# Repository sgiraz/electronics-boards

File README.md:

Electronics Boards
==================

This is the `electronics-boards` repository, containing all the electronic boards developed for study and DIY purposes.

Each board has an own folder where there are schematic, layout, firmware, simulations, documents, photos, configuration files, etc.

The board folders follow these rules:
- foldername **name of the board** 
- admitted subfolders:
   - **docs** folder contains documents
      - **datasheet** folder contains useful datasheet
      - **manuals** folder contains reference manual
   - **output** folder contains files for the production of the PCB and board (Gerber files, BOM, PCB Notes, etc.)
   - **kicad** folder contains the KiCad project
   - **pics** folder contains useful photos and videos of pcb, board, setup
   - **sw** folder contains the firmware useful for the board (test, normal operation, etc)
   
Note: folders and files must be named in lowercase

## Git LFS remark
This repository exploits the Git Large File Support ([LFS][1]) to handle the binary files.
To download the binary files, follow the GitHub [instructions][2]. To configure Git LFS, follow these [instructions][3].

[1]: https://git-lfs.github.com/
[2]: https://help.github.com/articles/installing-git-large-file-storage/
[3]: https://help.github.com/en/github/managing-large-files/configuring-git-large-file-storage

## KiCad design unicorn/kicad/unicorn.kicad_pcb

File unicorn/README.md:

# The Unicorn Board

## Overview

The Unicorn Board, designed by Simone Girardi in 2022, is a compact, Arduino-like programmable board. It's equipped with service LEDs for TX and RX, making it a versatile tool for various microcontroller projects.

## Features

- **ATmega328P Microcontroller**: Powers your projects.
- **16MHz Crystal Oscillator**: Provides a stable clock signal.
- **Input Voltage**: Accepts an external power supply ranging from 7V to 12V.
- **7805 Voltage Regulator**: Ensures a steady 5V supply to the microcontroller and other components.
- **TX and RX LEDs**: Offer visual feedback for data transmission and reception.
- **ISP Header**: Facilitates easy programming.
- **Reset Button**: Allows for easy resetting.

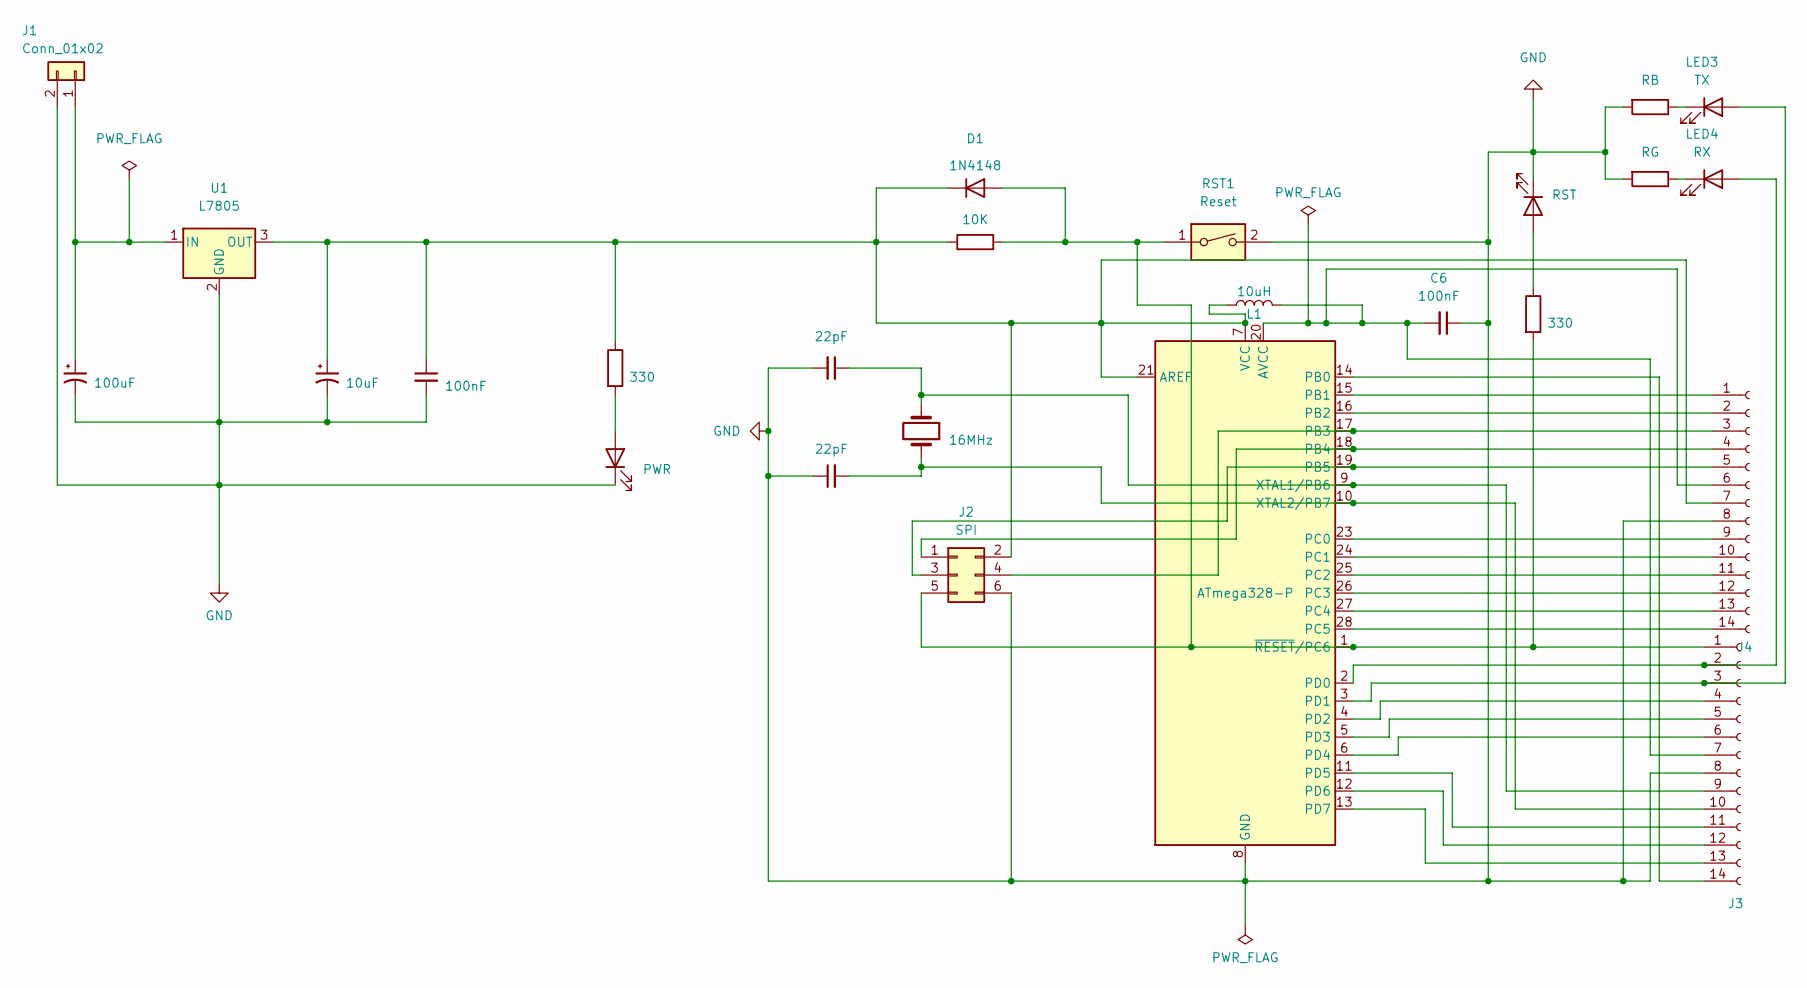
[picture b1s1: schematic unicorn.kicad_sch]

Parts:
C1: 100uF; CP_Radial_D5.0mm_P2.00mm
C2: 10uF; CP_Radial_D5.0mm_P2.00mm
C3, C6: 100nF; C_Disc_D3.8mm_W2.6mm_P2.50mm
C4, C5: 22pF; C_Disc_D3.8mm_W2.6mm_P2.50mm
Crystal1: 16MHz; Crystal_HC49-4H_Vertical
D1: 1N4148; D_DO-35_SOD27_P7.62mm_Horizontal
J1: Conn_01x02; JST_S2B-PH-SM4-TB
J2: SPI; PinHeader_2x03_P2.54mm_Vertical
J3, J4: Conn_01x14_Female; PinSocket_1x14_P2.54mm_Vertical
L1: 10uH; L_0805_2012Metric_Pad1.05x1.20mm_HandSolder
LED1: PWR; LED_D3.0mm
LED2: RST; LED_D3.0mm
LED3: TX; LED_0402_1005Metric
LED4: RX; LED_0402_1005Metric
R1, R3: 330; R_Axial_DIN0204_L3.6mm_D1.6mm_P5.08mm_Horizontal
R2: 10K; R_Axial_DIN0207_L6.3mm_D2.5mm_P10.16mm_Horizontal
R4: RB; R_0402_1005Metric
R5: RG; R_0402_1005Metric
RST1: Reset; SW_PUSH_6mm
U1: L7805; TO255P1020X450X2000-3
U2: ATmega328-P; DIP-28_W7.62mm

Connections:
GND: C1.2, C2.2, C3.2, C4.2, C5.1, C6.1, J1.2, J2.6, J3.8, J4.8, LED1.1 (K), LED2.1 (K), R4.2, R5.2, RST1.2, U1.2 (GND), U2.8 (GND), U2.22 (GND)
unnamed: D1.2 (A), J2.5, J3.1, R2.2, R3.2, RST1.1, U2.1 (~RESET/PC6)
unnamed: C2.1, C3.1, D1.1 (K), J2.2, J4.7, L1.1, R1.1, R2.1, U1.3 (OUT), U2.7 (VCC), U2.21 (AREF)
unnamed: C1.1, J1.1, U1.1 (IN)
unnamed: J2.1, J4.4, U2.18 (PB4)
unnamed: J2.3, J4.5, U2.19 (PB5)
unnamed: J2.4, J4.3, U2.17 (PB3)
unnamed: J3.2, LED4.2 (A), U2.2 (PD0)
unnamed: J3.3, LED3.2 (A), U2.3 (PD1)
unnamed: J3.4, U2.4 (PD2)
unnamed: J3.5, U2.5 (PD3)
unnamed: J3.6, U2.6 (PD4)
unnamed: C6.2, J3.7, J4.6, L1.2, U2.20 (AVCC)
unnamed: C4.1, Crystal1.1, J3.9, U2.9 (XTAL1/PB6)
unnamed: C5.2, Crystal1.2, J3.10, U2.10 (XTAL2/PB7)
unnamed: J3.11, U2.11 (PD5)
unnamed: J3.12, U2.12 (PD6)
unnamed: J3.13, U2.13 (PD7)
unnamed: J3.14, U2.14 (PB0)
unnamed: J4.1, U2.15 (PB1)
unnamed: J4.2, U2.16 (PB2)
unnamed: J4.9, U2.23 (PC0)
unnamed: J4.10, U2.24 (PC1)
unnamed: J4.11, U2.25 (PC2)
unnamed: J4.12, U2.26 (PC3)
unnamed: J4.13, U2.27 (PC4)
unnamed: J4.14, U2.28 (PC5)
unnamed: LED1.2 (A), R1.2
unnamed: LED2.2 (A), R3.1
unnamed: LED3.1 (K), R4.1
unnamed: LED4.1 (K), R5.1

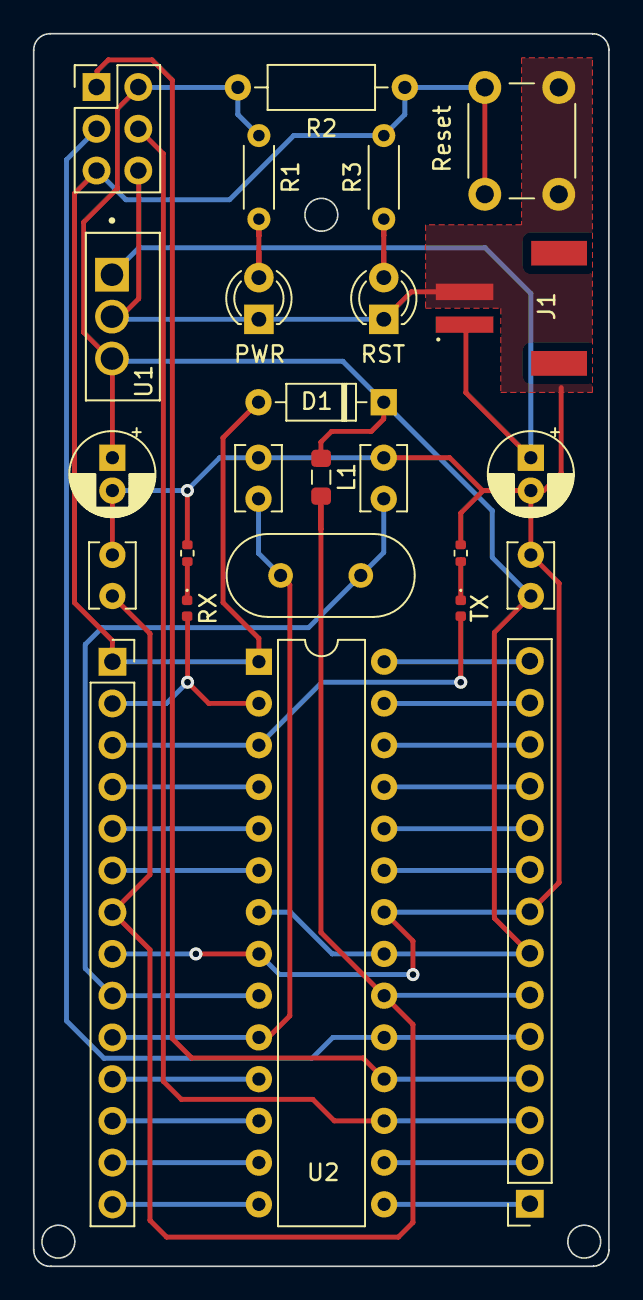
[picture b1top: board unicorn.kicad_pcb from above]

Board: 2 copper layers, 35.0 x 75.0 mm, 25 parts (0 on the bottom side), 31 nets.

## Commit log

2023-08-03 First commit: - add unicorn board - add gitignore - add datasheets
2023-08-04 update pcb: - add relative path to step file for L7805 component
2023-08-04 add fp anch sym table settings and fix the projects
2023-08-08 add step file of the unicorn board
2023-08-08 unicorn: update project file
2023-08-08 unicorn: remove step and add stl
2023-10-06 add issue template
2023-10-10 replace power connector - still need to redo routing
2024-01-04 fix routing + replace power connector with the right one
2024-01-05 add jst connector + update step file
2024-01-05 Unicorn - Feat/fix components (#2)
    * replace power connector
    - still need to redo routing
    * fix routing + replace power connector with the right one
    * add jst connector + update step file
2024-02-04 add .gitattributes for git LFS
2024-02-05 update unicorn board layout - minor improvements to the project footprints
2024-02-05 update img
2024-02-05 folder reorganization
2024-03-03 Add mounting holes
2024-03-03 update unicorn asset
